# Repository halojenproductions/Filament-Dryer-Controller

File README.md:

# Filament Dryer Controller
## Overview
## Details
something something filament something something dry
### Processor
- ATMega328P
### Inputs
#### Button
- Pin D2
- Momentary
- Internal pull-up
#### PTC thermistor
- Pin A0
- B3950
- 100KΩ @25°C
- B-value 3950 @50°C
- 100KΩ external pull-down
#### Temperature & humudity sensor
- I2C 0x44
- SHT30-D
### Outputs
#### Ok LED
- Pin D12
- Yellow
#### Heating LED
- Pin D13
- Red
#### Display
- I2C 0x78
- 128X64 Monochrome OLED
- SH1106

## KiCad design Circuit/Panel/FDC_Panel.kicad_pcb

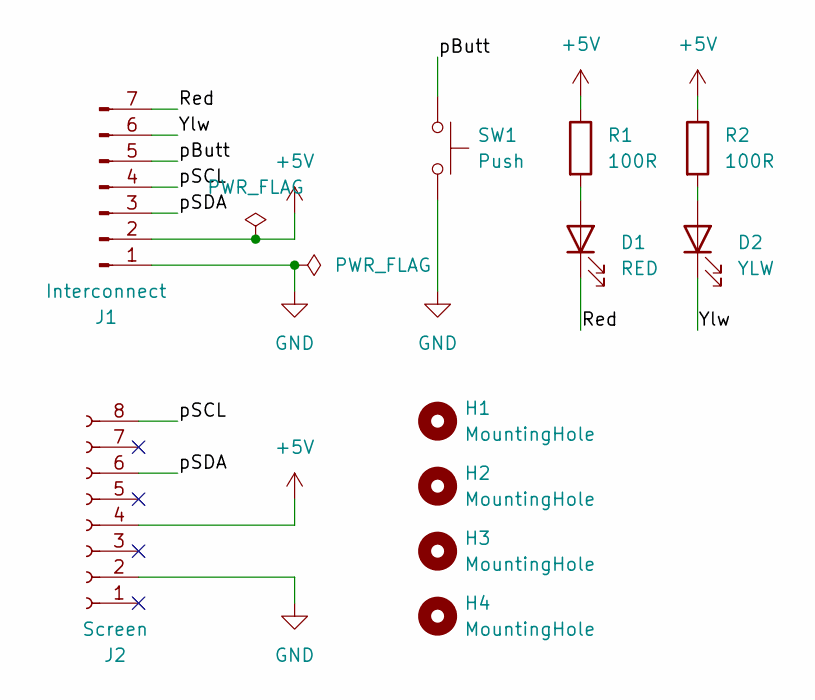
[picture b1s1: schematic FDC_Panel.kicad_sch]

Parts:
D1: RED; LED_D3.0mm_Clear_Flush
D2: YLW; LED_D3.0mm_Clear_Flush
H1, H2, H3, H4: MountingHole; MountingHole_2.2mm_M2
J1: Interconnect; JST_XH_S7B-XH-A_1x07_P2.50mm_Horizontal
J2: Screen; SAMTEC_HLE-104-02-F-DV-BE
R1, R2: 100R; R_1206_3216Metric
SW1: Push; Push_Button_PTS641-S-K-31

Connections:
+5V: J1.2, J2.4, R1.1, R2.1
/Red: D1.1 (K), J1.7
/Ylw: D2.1 (K), J1.6
/pButt: J1.5, SW1.2
/pSCL: J1.4, J2.8
/pSDA: J1.3, J2.6
GND: J1.1, J2.2, SW1.1
unnamed: D1.2 (A), R1.2
unnamed: D2.2 (A), R2.2

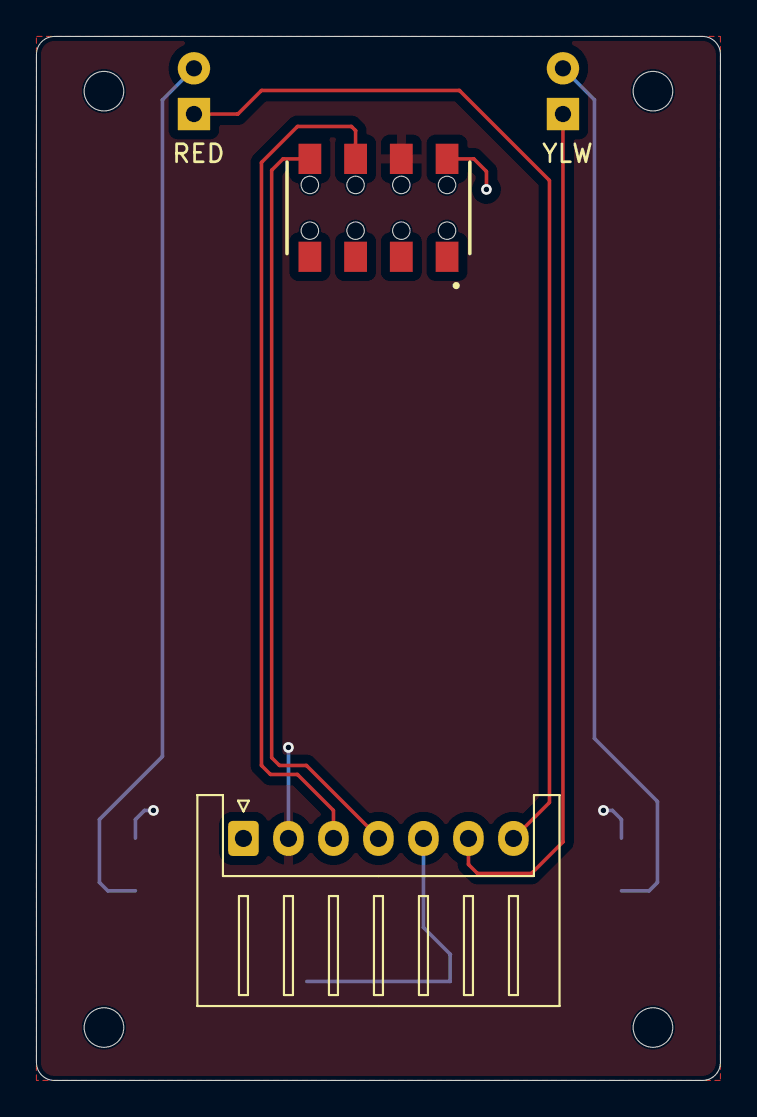
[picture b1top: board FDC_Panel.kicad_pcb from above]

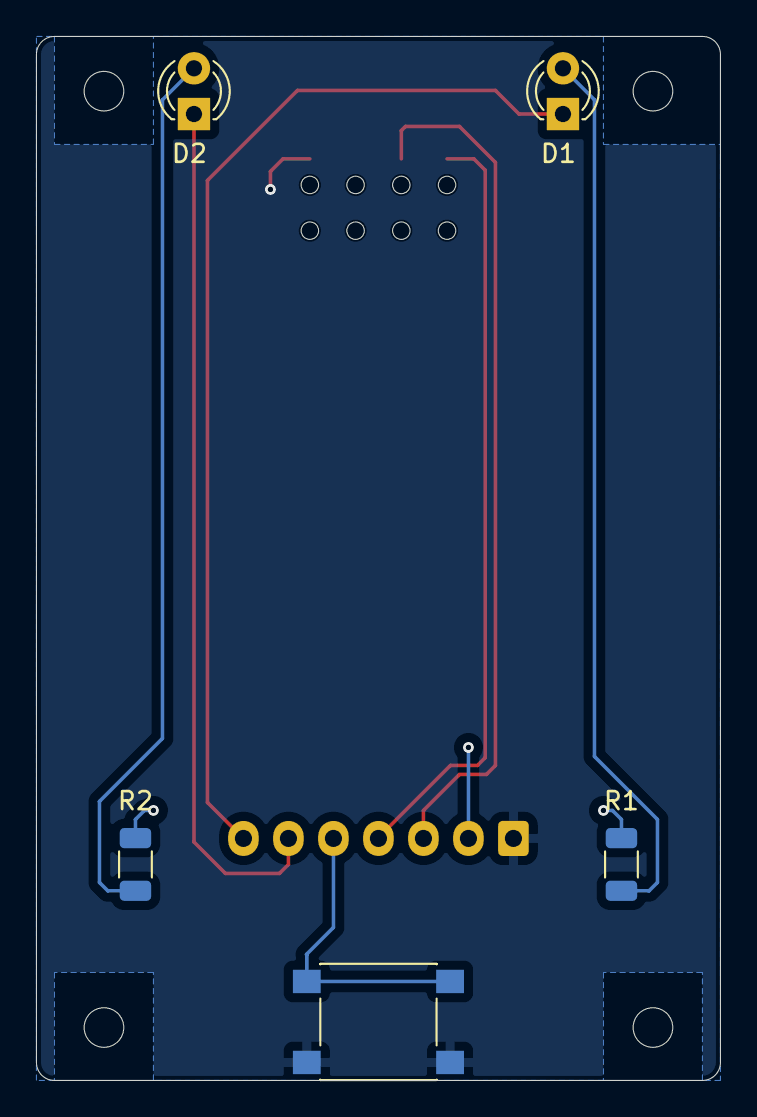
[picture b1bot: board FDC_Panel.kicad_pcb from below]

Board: 2 copper layers, 38.0 x 58.0 mm, 11 parts (5 on the bottom side), 9 nets.

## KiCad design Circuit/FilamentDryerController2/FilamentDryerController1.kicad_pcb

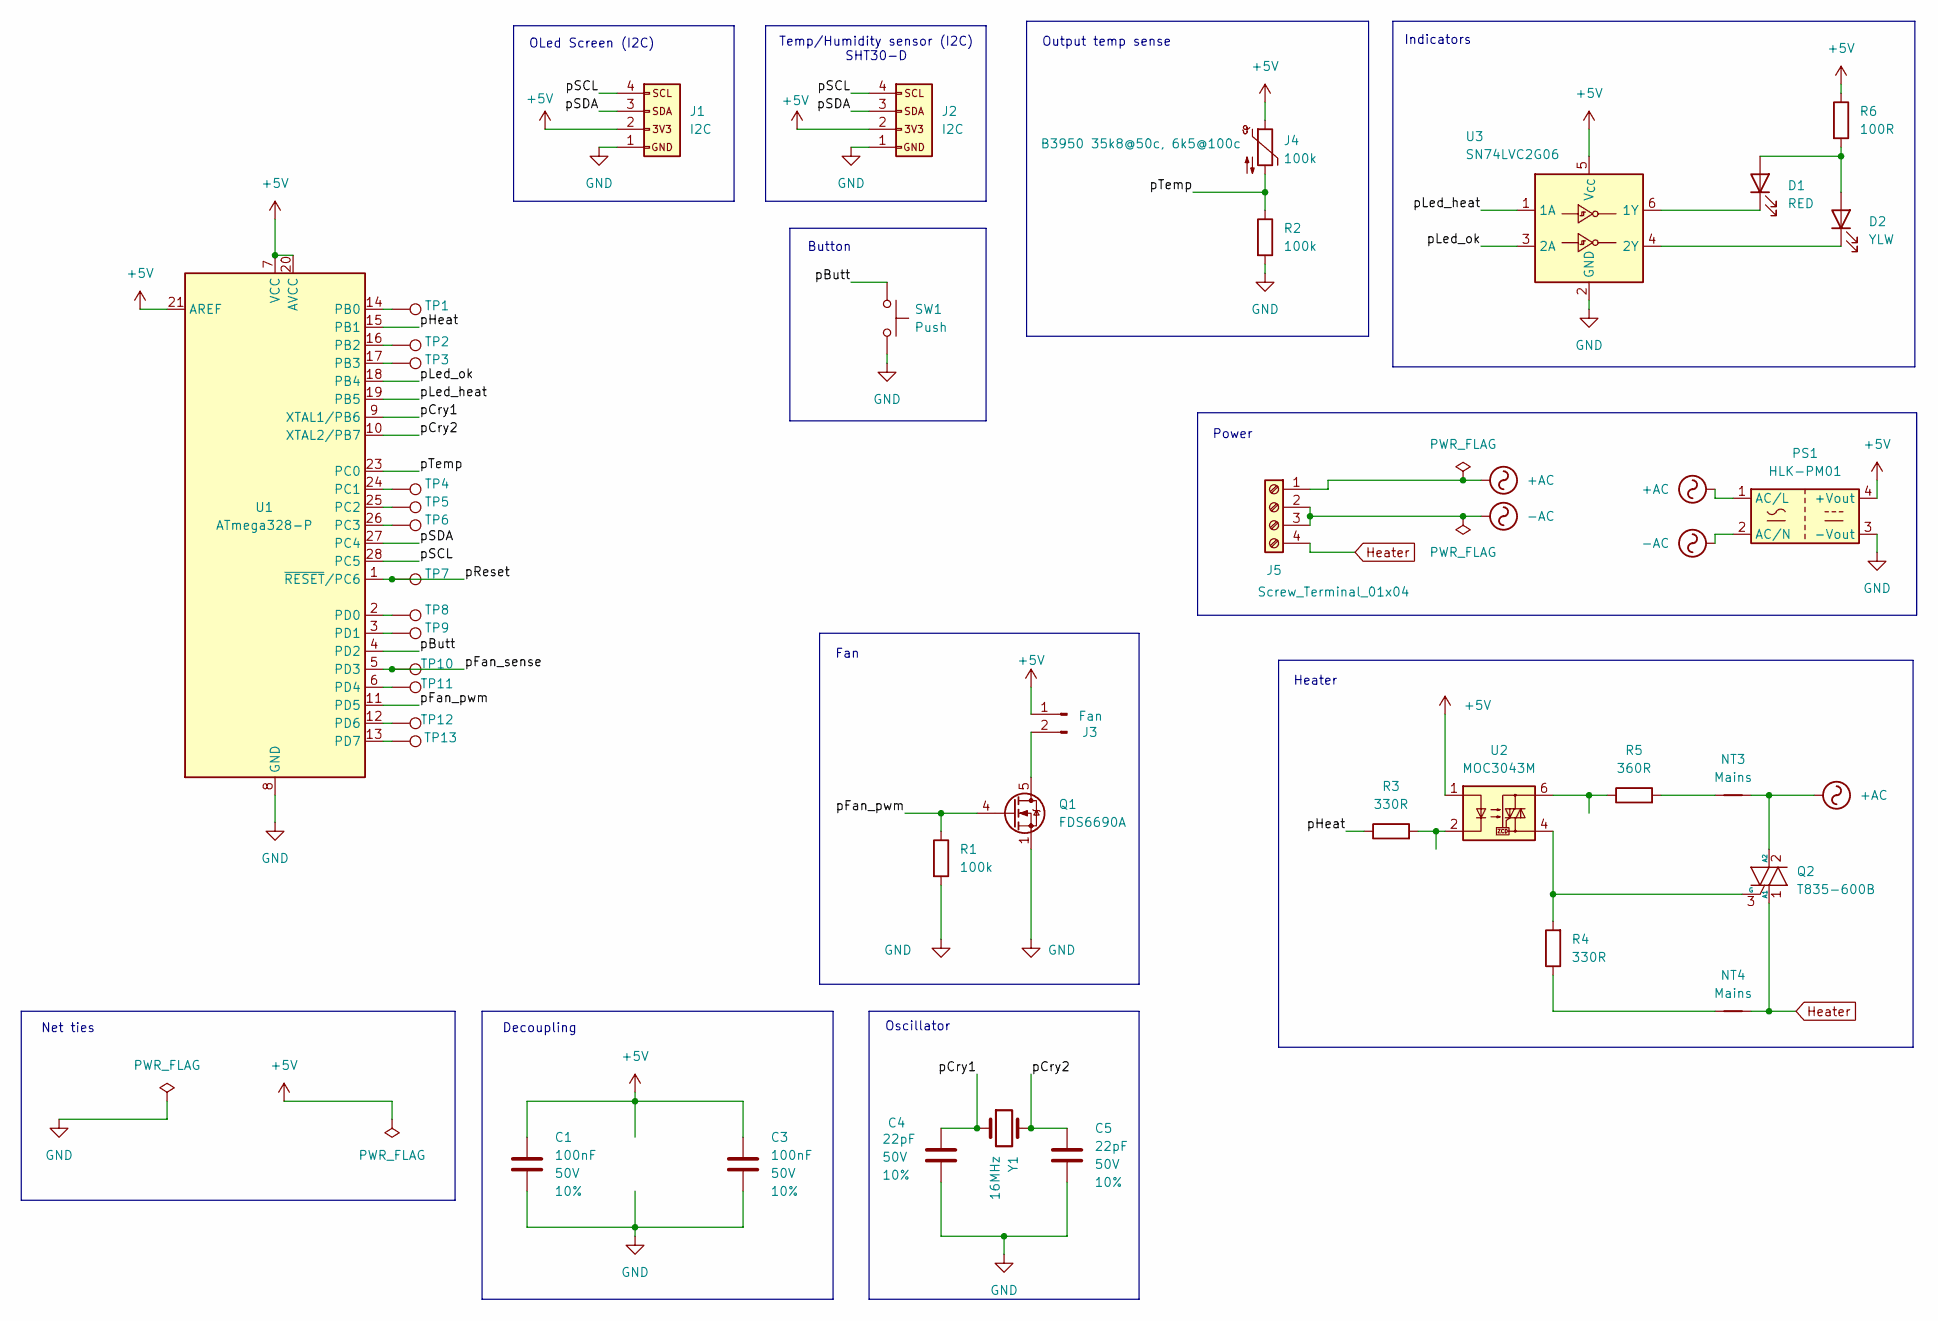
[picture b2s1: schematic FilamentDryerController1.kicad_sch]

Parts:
C1, C3: 100nF; C_1206_3216Metric; Voltage 50V; Tolerance 10%
C4, C5: 22pF; C_1206_3216Metric; Voltage 50V; Tolerance 10%
D1: RED; LED_1206_3216Metric
D2: YLW; LED_1206_3216Metric
J1, J2: I2C; JST_XH_B4B-XH-A_1x04_P2.50mm_Vertical
J3: Fan; JST_XH_B2B-XH-A_1x02_P2.50mm_Vertical
J4: 100k; JST_XH_B2B-XH-A_1x02_P2.50mm_Vertical
J5: Screw_Terminal_01x04; Screw_Terminal_3.5mm-4
NT3, NT4: Mains; NetTie-2_SMD_Pad0.2x2.5mm
PS1: HLK-PM01; Converter_ACDC_Hi-Link_HLK-PMxx
Q1: FDS6690A; SOIC-8_3.9x4.9mm_P1.27mm
Q2: T835-600B; TO-252-2
R1, R2: 100k; R_1206_3216Metric
R3, R4: 330R; R_1206_3216Metric
R5: 360R; R_1206_3216Metric
R6: 100R; R_1206_3216Metric
SW1: Push; SW_SPST_PTS645
TP1: PB0; TestPoint-1.25mm
TP2: PB2; TestPoint-1.25mm
TP3: PB3; TestPoint-1.25mm
TP4: PC1; TestPoint-1.25mm
TP5: PC2; TestPoint-1.25mm
TP6: PC3; TestPoint-1.25mm
TP7: PC6; TestPoint-1.25mm
TP8: PD0; TestPoint-1.25mm
TP9: PD1; TestPoint-1.25mm
TP10: PD3; TestPoint-1.25mm
TP11: PD4; TestPoint-1.25mm
TP12: PD6; TestPoint-1.25mm
TP13: PD7; TestPoint-1.25mm
U1: ATmega328-P; DIP-28_W7.62mm_Socket_LongPads
U2: MOC3043M; SMDIP-6_W9.53mm
U3: SN74LVC2G06; SOT-23-6
Y1: 16MHz; Crystal_HC49-U_Vertical

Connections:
+5V: C1.1, C3.1, J1.2, J2.2, J3.1, J4.1, PS1.4 (+Vout), R6.1, U1.7 (VCC), U1.20 (AVCC), U1.21 (AREF), U2.1, U3.5 (V_{CC})
+AC: J5.1, NT3.2, PS1.1 (AC/L), Q2.2 (A2)
-AC: J5.2, J5.3, PS1.2 (AC/N)
/pButt: SW1.2, U1.4 (PD2)
/pCry1: C4.1, U1.9 (XTAL1/PB6), Y1.1
/pCry2: C5.2, U1.10 (XTAL2/PB7), Y1.2
/pFan_pwm: Q1.4 (G), R1.1, U1.11 (PD5)
/pFan_sense: TP10.1, U1.5 (PD3)
/pHeat: R3.1, U1.15 (PB1)
/pLed_heat: U1.19 (PB5), U3.1 (1A)
/pLed_ok: U1.18 (PB4), U3.3 (2A)
/pReset: TP7.1, U1.1 (~RESET/PC6)
/pSCL: J1.4, J2.4, U1.28 (PC5)
/pSDA: J1.3, J2.3, U1.27 (PC4)
/pTemp: J4.2, R2.1, U1.23 (PC0)
GND: C1.2, C3.2, C4.2, C5.1, J1.1, J2.1, PS1.3 (-Vout), Q1.1 (S), Q1.2 (S), Q1.3 (S), R1.2, R2.2, SW1.1, U1.8 (GND), U1.22 (GND), U3.2 (GND)
Heater: J5.4, NT4.2, Q2.1 (A1)
unnamed: D1.2 (A), D2.2 (A), R6.2
unnamed: D1.1 (K), U3.6 (1Y)
unnamed: D2.1 (K), U3.4 (2Y)
unnamed: J3.2, Q1.5 (D), Q1.6 (D), Q1.7 (D), Q1.8 (D)
unnamed: NT3.1, R5.2
unnamed: NT4.1, R4.1
unnamed: Q2.3 (G), R4.2, U2.4
unnamed: R3.2, U2.2
unnamed: R5.1, U2.6
unnamed: TP1.1, U1.14 (PB0)
unnamed: TP2.1, U1.16 (PB2)
unnamed: TP3.1, U1.17 (PB3)
unnamed: TP4.1, U1.24 (PC1)
unnamed: TP5.1, U1.25 (PC2)
unnamed: TP6.1, U1.26 (PC3)
unnamed: TP8.1, U1.2 (PD0)
unnamed: TP9.1, U1.3 (PD1)
unnamed: TP11.1, U1.6 (PD4)
unnamed: TP12.1, U1.12 (PD6)
unnamed: TP13.1, U1.13 (PD7)

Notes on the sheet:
Button
Power
Fan
Net ties
OLed Screen (I2C)
Decoupling
Heater
Indicators
Oscillator
Temp/Humidity sensor (I2C) SHT30-D
Output temp sense

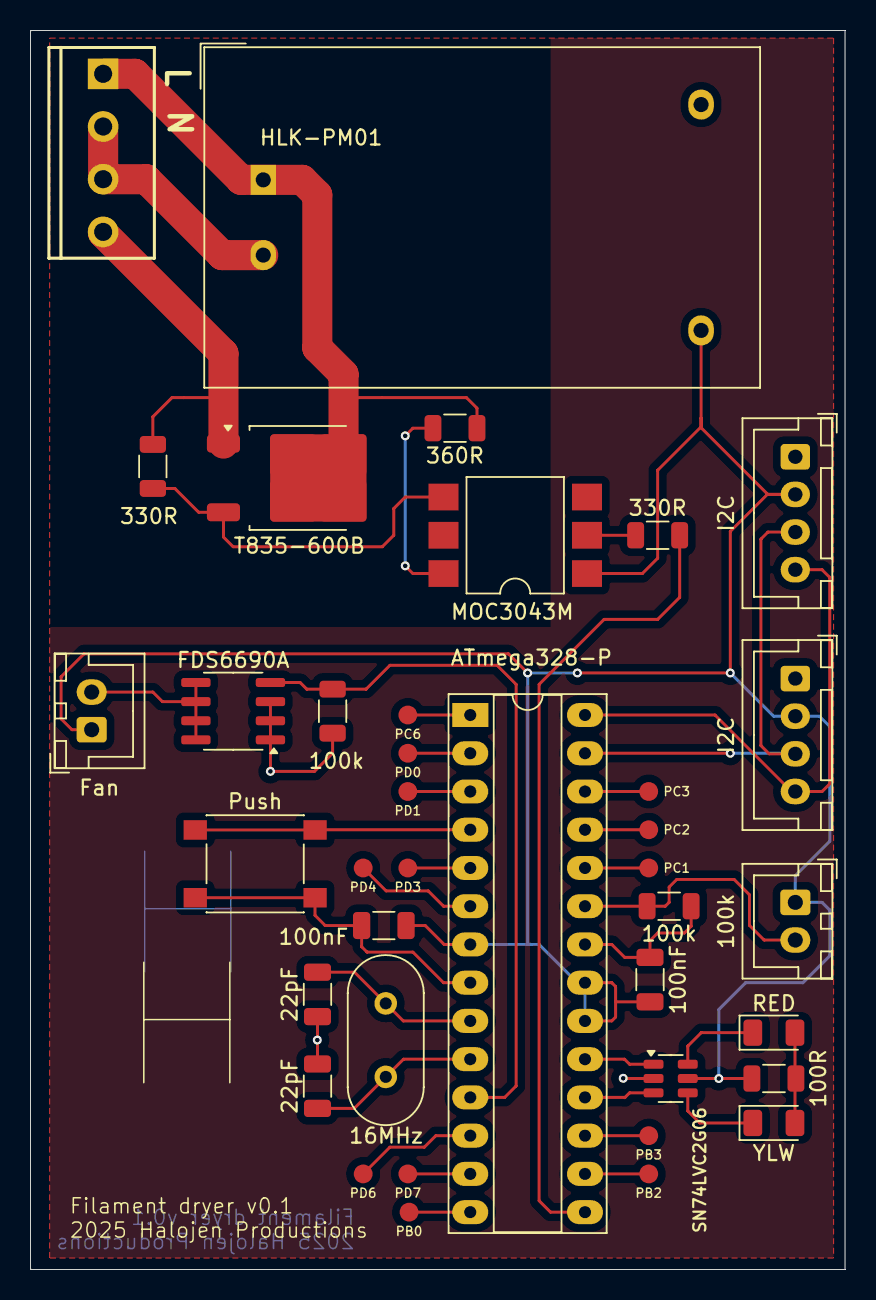
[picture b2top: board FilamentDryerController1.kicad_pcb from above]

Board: 2 copper layers, 54.1 x 82.3 mm, 40 parts (0 on the bottom side), 37 nets.

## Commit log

2025-01-03 Changed heat to AC. Still need to figure out fan.
2025-01-04 Pcb done.
2025-01-04 Removed cache.
2025-01-18 First pcb prototype fabricated.
2025-02-01 Better bom.
2025-02-14 PCB fabricated.
2025-04-13 Blinking.
2025-04-13 Screen working.
2025-04-15 Formatting working properly. Added status class.
2025-04-15 Updated .gitignore
2025-04-18 Ops, commands, temps (wrong)
2025-04-18 Gitignore corrected.
2025-04-18 Temp unit tests working (with wide tolerance).
2025-04-18 Some info displaying.
2025-04-18 Now showing target humidity.
2025-04-18 All info displaying.
2025-04-19 Unit tests solid as.
2025-04-19 Timer class.
2025-04-19 Timer tests.
2025-04-19 Interrupt done. And some user interaction.
2025-04-19 Weird bugs. I'll have to use methods for getting filaments.
2025-04-20 Working correctly.
2025-04-20 Draw areas added.
2025-04-20 Moved screen into UI.
2025-04-20 Screen updates moved to UI.
2025-04-20 Screen drawing done and tidied.
2025-04-20 Added checkDirty.
2025-04-20 Interaction is perfect.
2025-04-20 Code style might be perfect now.
2025-04-20 Format didn't change much.
    Thought i was crazy for a few hours. Turns out i just found a bug in clang format and was wasting my time.
2025-04-21 Saves & loads.
2025-04-21 Added task list. Tweaked gitignore to include settings.json.
2025-04-21 Repo readme
2025-04-21 Renamed temperature to thermistor. Started hum/temp sensor.
2025-04-21 Simplified Thermistor. Added sensor checks.
2025-04-21 Swapped humidity & temp sides.
2025-04-21 Updated the task list.
2025-04-22 Tidies.
2025-04-23 Added humidity tests.
2025-04-23 Redid operations tests to match humidity tests.
2025-04-23 All test access getters/setters overloaded.
2025-04-23 Sensor temp tests.
2025-04-23 Updated task list.
2025-04-23 Moved screen stuff to UI.
2025-04-23 Started control loop. Moved pins to Pins namespace.
2025-04-23 Fixed millis bug i just introduced when moving currentTime to Ops.
2025-04-24 Active control loop mostly done.
2025-04-25 Completely broken. Not enough RAM.
    I'm going to start again.
2025-04-25 Stripped down, but buggy.
    And only slightly smaller than before so i wasted my time.
2025-04-25 Some unit tests to help find the bugs.
2025-04-26 Tests done.
2025-04-26 Slight tidying.
2025-04-26 Button hold bug fixed. Partial frame buffer.
    Yeah.. rewriting the whole thing only saved about 1% or RAM and still ran out. So now we have shitty code AND shitty screen refresh. I did so much improvement on the button logic that I don't want to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
2025-04-26 Mostly done. But don't look at the tests.
2025-04-27 Brought some stuff back from the old project.
2025-04-27 Tests messy, but done (yet again).
2025-04-27 Fixed bug and test.
    Tests are only useful if they run (and test the things that need testing).
2025-04-29 Panel storted.
2025-04-30 Retention frame started.
2025-05-02 Frame now with holes.
2025-05-02 Screen shroud. Separated export models.
2025-05-03 Screws through both pcbs. Not going to work.
2025-05-04 Frame screws back to the outside.
2025-05-04 Started control tests.
2025-05-11 Added UI symbols.
2025-05-11 Added distinct error states + tests.
2025-05-11 Better resettable error check.
2025-05-11 Added terminal error check function.
2025-05-13 Button added.
2025-05-13 Changed to assembly approach.
2025-05-13 Ditched the annoying screen viewport -2 thing.
2025-05-13 Tweaks.
2025-05-14 Button looking good.
2025-05-17 Button redesign.
2025-05-17 Tiny button tweak.
2025-05-18 Pcb screw posts + some tweaks.
2025-05-20 Frame redesign.
2025-05-20 Button redesign again.
2025-05-24 Added the back.
2025-05-31 Lenses added. Back tweaked for printability.
2025-05-31 Now using shared export script.
2025-05-31 Removed error status.
2025-05-31 Added test to prove timer check will handle millis() overflow.
2025-05-31 Status tweaks.
2025-05-31 Added some filament profiles.
2025-06-01 Implemented Moist. Started control tests.
2025-06-07 Panel PCB, rendered mock, low profile header.
2025-06-07 Button anchor full width.
2025-06-07 Panel PCB almost done.
2025-06-07 Cleaned up.
2025-06-07 Updated gitignore.
2025-09-21 Nested projects.
2025-09-21 Main started.
2025-09-21 Progress.
2025-09-23 Slight redesign.
2025-09-28 Added a fan teardrop hole.
2025-09-28 Trying to decide where to put the sensor.
2025-10-03 I think i finally figured out the heater position.
2025-10-03 Electronics cavity.
2025-10-03 Rearranged files. Separated top from base.
2025-10-04 Cover started, interface mostly done.
2025-10-05 Top screws & shrouds.
2025-10-05 Started redesigning.
2025-10-11 More new positions sorted.
2025-10-11 Working on interface.
2025-10-12 Base interface & clips largely done.
2025-10-12 Interface pretty much done.
2025-10-12 Eliminated the intake section.
2025-10-12 Intake panel started.
2025-10-12 Intake positive done.
2025-10-13 Intake negative done.
2025-10-13 Meh.
2026-01-16 Started desiccant box. KiCad 9.
2026-01-16 More desiccant box progress.
2026-01-16 More box progress.
2026-01-16 Added support that's needed because i'm a dumass.
2026-01-17 Makercoin started.
